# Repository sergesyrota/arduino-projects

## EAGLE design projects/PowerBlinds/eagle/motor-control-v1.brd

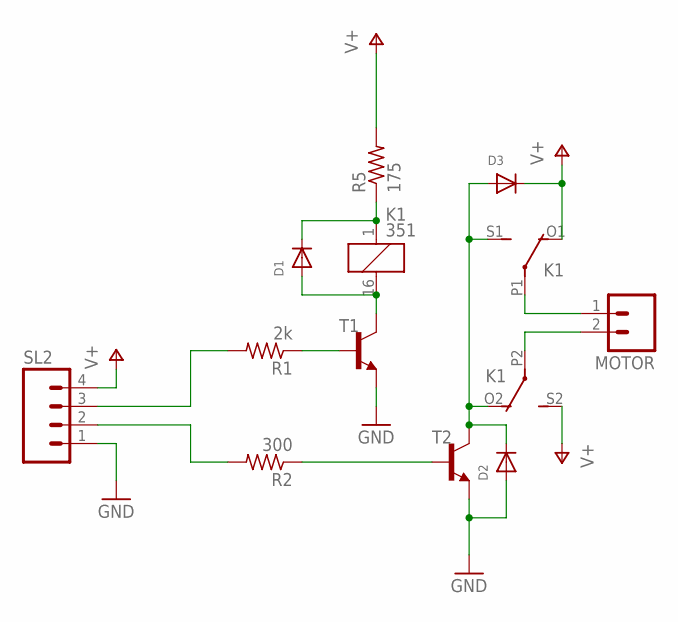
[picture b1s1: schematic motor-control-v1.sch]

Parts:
D1, D2, D3: DIODESMA; SMADIODE
K1: 351
MOTOR: M02; 02P
R1: 2k; R0603
R2: 300; R0603
R5: 175; R0603
SL2: M04; 04P
T1, T2: BC808-NPN-SOT23-BEC; SOT23-BEC

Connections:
GND: D2.A, SL2.1, T1.E, T2.E
unnamed: R2.2, SL2.2
unnamed: R1.2, SL2.3
unnamed: K1.P1, MOTOR.1
unnamed: K1.P2, MOTOR.2
unnamed: D2.C, D3.A, K1.O2 (O), K1.S1 (S), T2.C
unnamed: D1.A, K1.16 (2), T1.C
unnamed: D1.C, K1.1, R5.1
unnamed: R1.1, T1.B
unnamed: R2.1, T2.B
V+: D3.C, K1.O1 (O), K1.S2 (S), R5.2, SL2.4

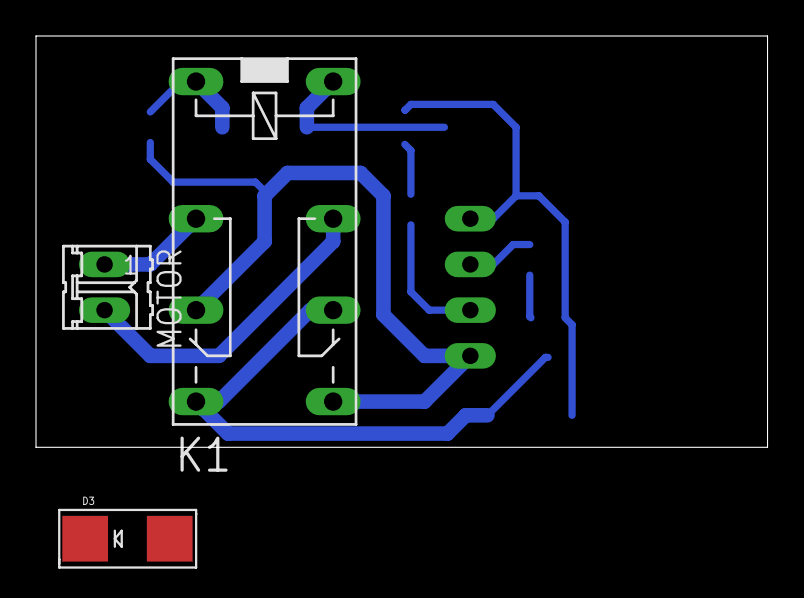
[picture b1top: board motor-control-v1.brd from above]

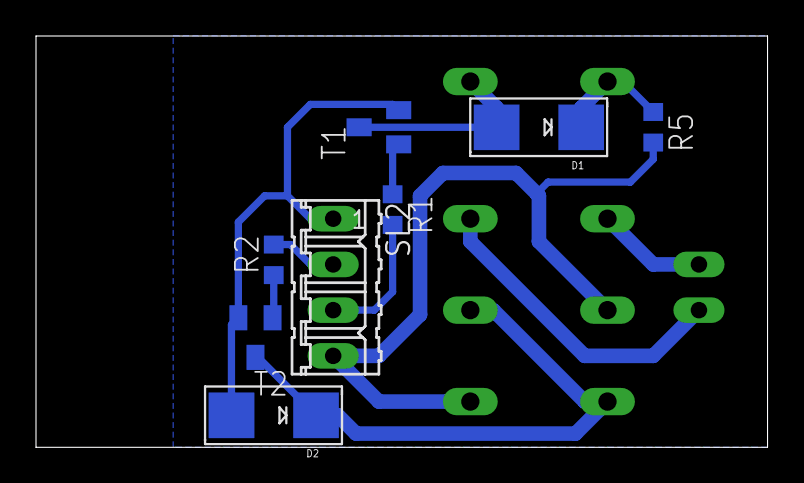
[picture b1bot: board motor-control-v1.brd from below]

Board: 2 copper layers, 40.6 x 22.9 mm, 11 parts (8 on the bottom side), 11 nets.

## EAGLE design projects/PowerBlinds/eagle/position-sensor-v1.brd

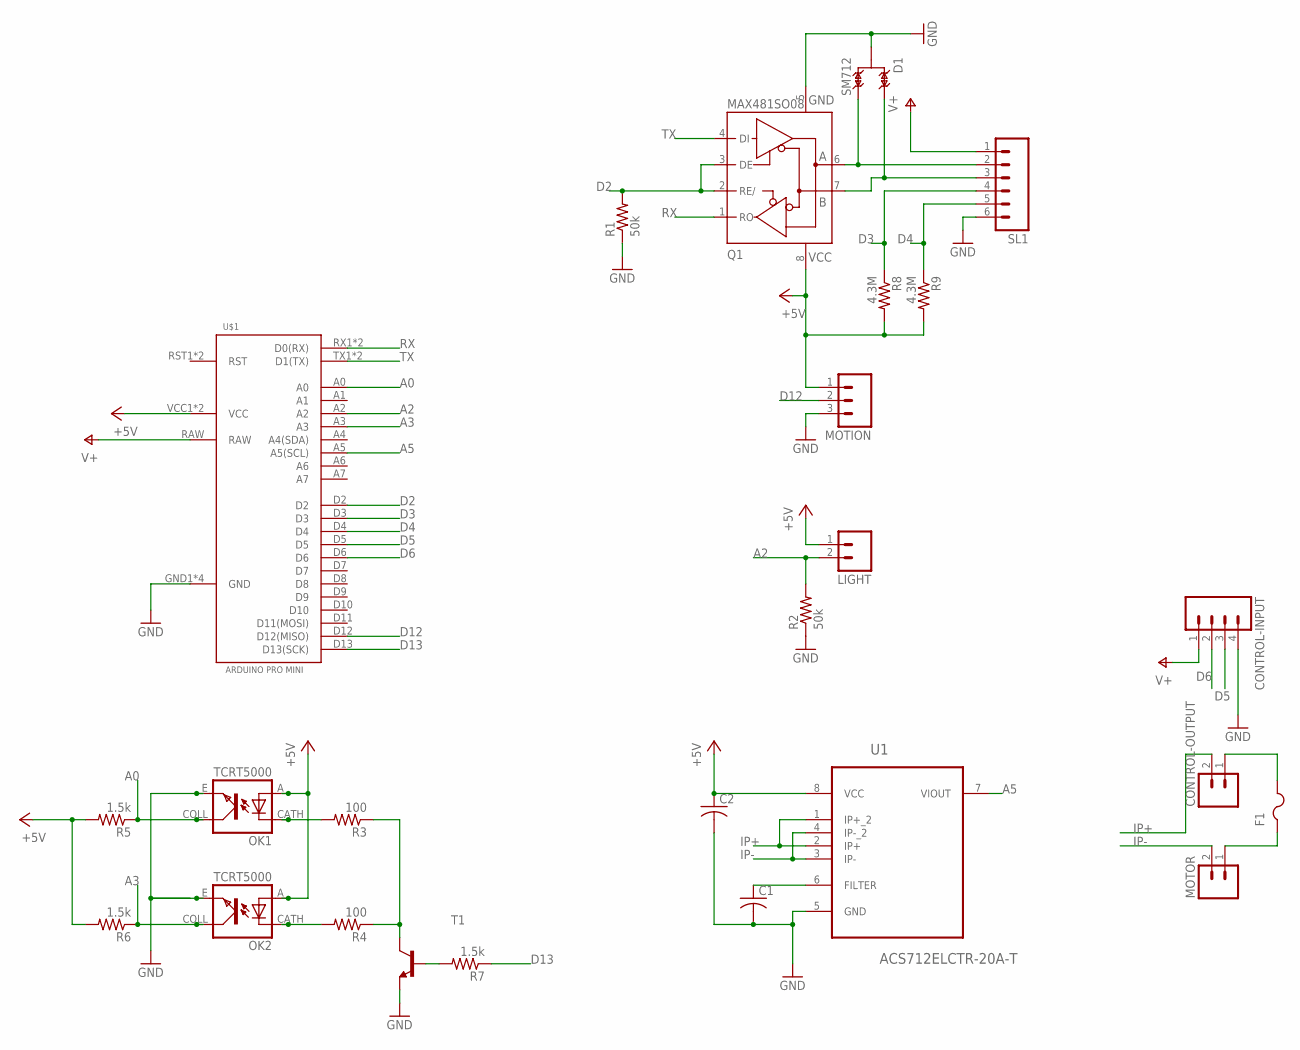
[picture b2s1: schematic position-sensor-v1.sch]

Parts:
C1, C2: C-USC0603K; C0603K
CONTROL-INPUT: M04; 04P
CONTROL-OUTPUT: M02; 02P
D1: SM712; SOT23-3
F1: PTCFUSE-1812; 1812
LIGHT: M02; 02P
MOTION: M03; 03P
MOTOR: M02; 02P
OK1, OK2: TCRT5000
Q1: MAX481SO08; SO08
R1, R2: 50k; R0603
R3, R4: 100; R0603
R5, R6, R7: 1.5k; R0603
R8, R9: 4.3M; R0603
SL1: M06; 06P
T1: BC808-NPN-SOT23-BEC; SOT23-BEC
U1: ACS712ELCTR-20A-T; SOIC127P600X175-8N
U$1: ARDUINO-PRO-MINI

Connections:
+5V: C2.1, LIGHT.1, MOTION.1, OK1.A, OK2.A, Q1.8 (+5V), R5.2, R6.2, R8.2, R9.2, U1.8 (VCC), U$1.VCC1 (VCC), U$1.VCC2 (VCC)
A0: OK1.COLL (COL), R5.1, U$1.A0
A2: LIGHT.2, R2.2, U$1.A2
A3: OK2.COLL (COL), R6.1, U$1.A3
A5: U1.7 (VIOUT), U$1.A5 (A5(SCL))
D2: Q1.2 (RE/), Q1.3 (DE), R1.2, U$1.D2
D3: R8.1, SL1.4, U$1.D3
D4: R9.1, SL1.5, U$1.D4
D5: CONTROL-INPUT.3, U$1.D5
D6: CONTROL-INPUT.2, U$1.D6
D12: MOTION.2, U$1.D12 (D12(MISO))
D13: R7.1, U$1.D13 (D13(SCK))
GND: C1.2, C2.2, CONTROL-INPUT.4, D1.3, MOTION.3, OK1.E (EMI), OK2.E (EMI), Q1.5 (GND), R1.1, R2.1, SL1.6, T1.E, U1.5 (GND), U$1.GND1 (GND), U$1.GND2 (GND), U$1.GND3 (GND), U$1.GND4 (GND)
IP+: CONTROL-OUTPUT.2, U1.1 (IP+_2), U1.2 (IP+)
IP-: MOTOR.2, U1.3 (IP-), U1.4 (IP-_2)
unnamed: D1.1, Q1.6 (A), SL1.2
unnamed: D1.2, Q1.7 (B), SL1.3
unnamed: F1.1, MOTOR.1
unnamed: OK1.CATH (C), R3.2
unnamed: OK2.CATH (C), R4.2
unnamed: CONTROL-OUTPUT.1, F1.2
unnamed: R7.2, T1.B
unnamed: R3.1, R4.1, T1.C
unnamed: C1.1, U1.6 (FILTER)
RX: Q1.1 (RO), U$1.RX1 (D0(RX)), U$1.RX2 (D0(RX))
TX: Q1.4 (DI), U$1.TX1 (D1(TX)), U$1.TX2 (D1(TX))
V+: CONTROL-INPUT.1, SL1.1, U$1.RAW

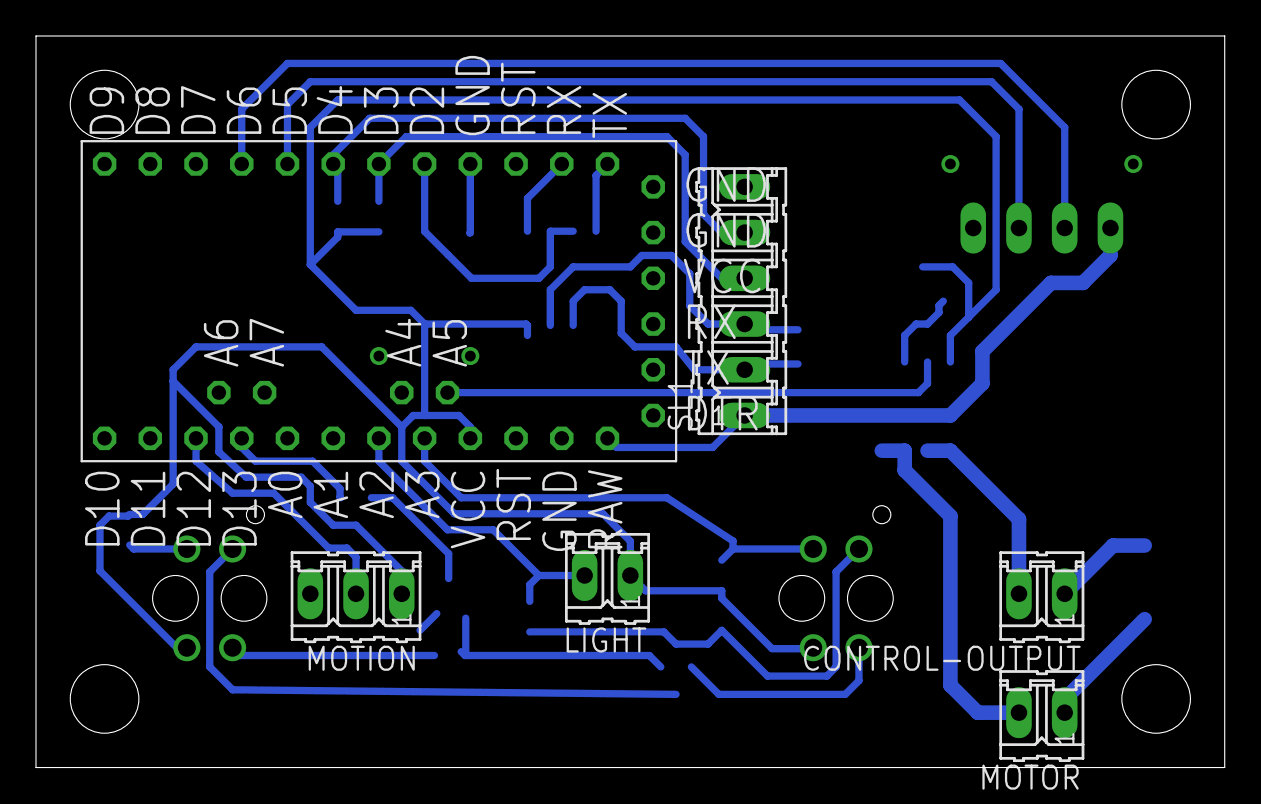
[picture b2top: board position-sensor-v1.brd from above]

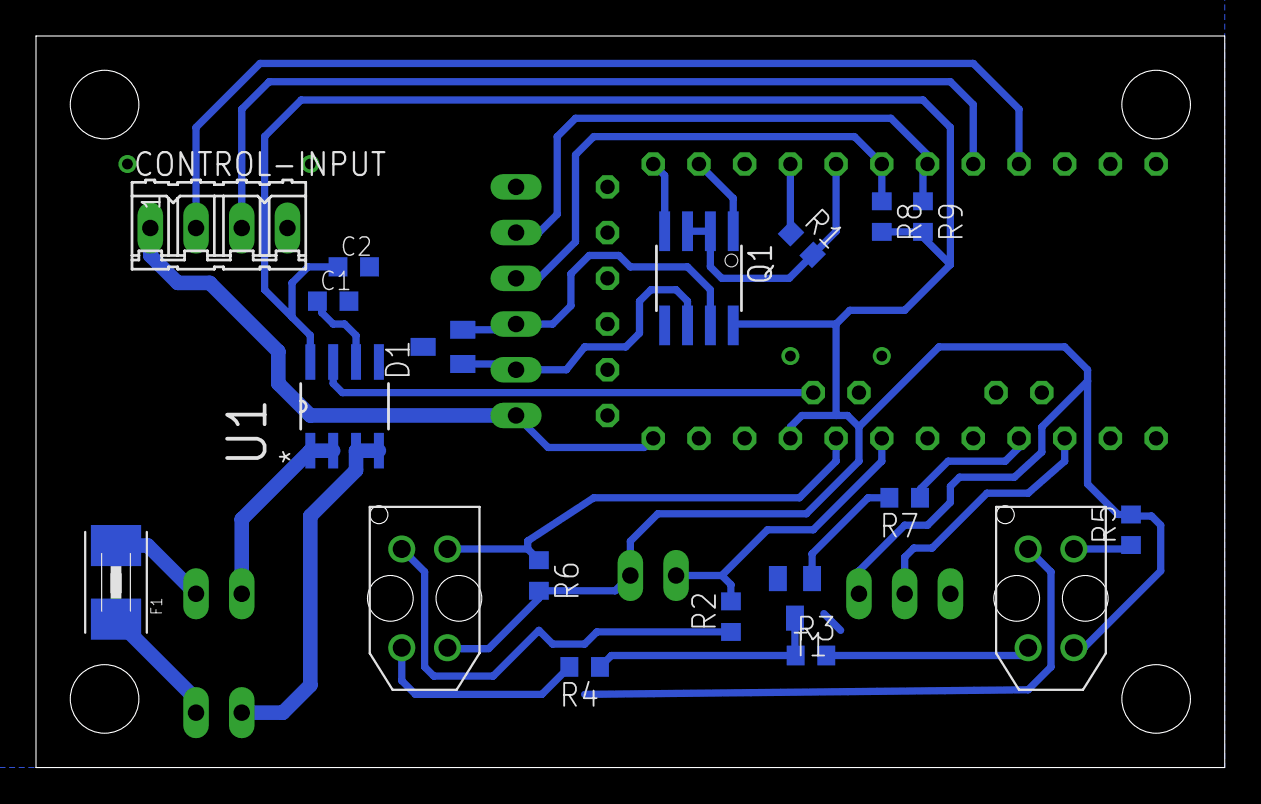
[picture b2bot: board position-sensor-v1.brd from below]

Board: 2 copper layers, 66.0 x 40.6 mm, 25 parts (19 on the bottom side), 27 nets.

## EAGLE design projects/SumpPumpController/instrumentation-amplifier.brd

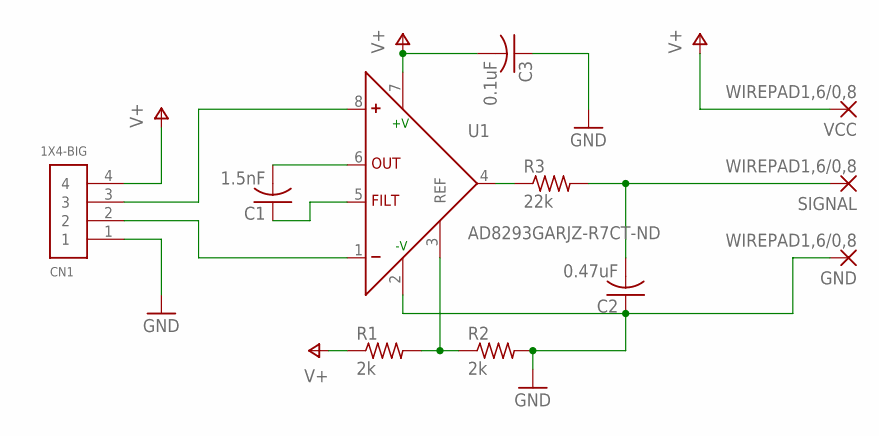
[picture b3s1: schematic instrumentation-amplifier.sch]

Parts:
C1: 1.5nF; C025-024X044
C2: 0.47uF; C050-024X044
C3: 0.1uF; C050-024X044
CN1: 1X4-BIG; 1X04-BIG
GND: WIREPAD1,6/0,8; 1,6/0,8
R1, R2: 2k; R0603
R3: 22k; R0603
SIGNAL: WIREPAD1,6/0,8; 1,6/0,8
U1: AD8293GARJZ-R7CT-ND; SOT23-8
VCC: WIREPAD1,6/0,8; 1,6/0,8

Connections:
GND: C2.1, C3.1, CN1.1, GND.1, R2.2, U1.2 (-V)
unnamed: C1.2, U1.6 (OUT)
unnamed: C1.1, U1.5 (FILT)
unnamed: R1.2, R2.1, U1.3 (REF)
unnamed: C2.2, R3.2, SIGNAL.1
unnamed: CN1.3, U1.8 (+)
unnamed: CN1.2, U1.1 (-)
unnamed: R3.1, U1.4 (ADC-OUT)
V+: C3.2, CN1.4, R1.1, U1.7 (+V), VCC.1

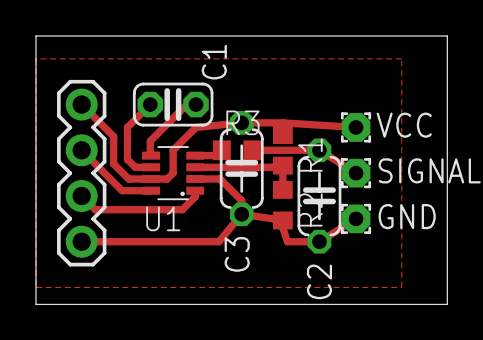
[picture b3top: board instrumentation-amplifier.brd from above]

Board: 2 copper layers, 22.9 x 14.9 mm, 11 parts (0 on the bottom side), 9 nets.

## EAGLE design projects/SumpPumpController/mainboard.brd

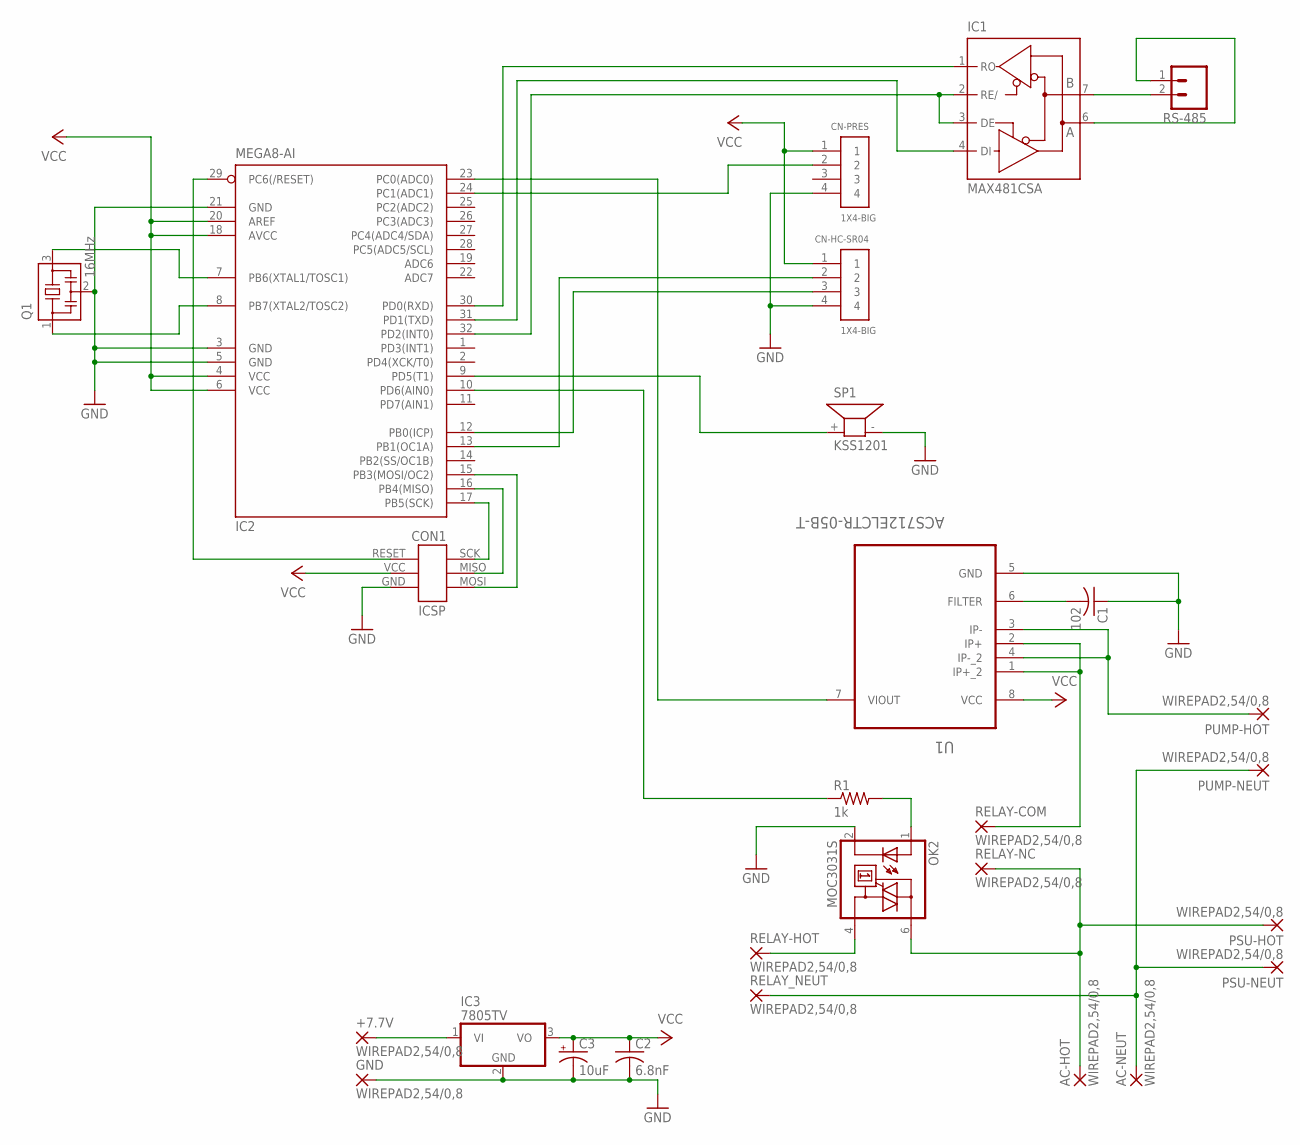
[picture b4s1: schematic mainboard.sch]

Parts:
+7.7V: WIREPAD2,54/0,8; 2,54/0,8
AC-HOT: WIREPAD2,54/0,8; 2,54/0,8
AC-NEUT: WIREPAD2,54/0,8; 2,54/0,8
C1: 102; C025-024X044
C2: 6.8nF; C050-024X044
C3: 10uF; E1,8-4
CN-HC-SR04: 1X4-BIG; 1X04-BIG
CN-PRES: 1X4-BIG; 1X04-BIG
CON1: ICSP-HEADER
GND: WIREPAD2,54/0,8; 2,54/0,8
IC1: MAX481CSA; SO08
IC2: MEGA8-AI; TQFP32-08
IC3: 7805TV; TO220V
OK2: MOC3031S; DIL6-SMD
PSU-HOT: WIREPAD2,54/0,8; 2,54/0,8
PSU-NEUT: WIREPAD2,54/0,8; 2,54/0,8
PUMP-HOT: WIREPAD2,54/0,8; 2,54/0,8
PUMP-NEUT: WIREPAD2,54/0,8; 2,54/0,8
Q1: 16MHz; RESONATOR
R1: 1k; R0603
RELAY-COM: WIREPAD2,54/0,8; 2,54/0,8
RELAY-HOT: WIREPAD2,54/0,8; 2,54/0,8
RELAY-NC: WIREPAD2,54/0,8; 2,54/0,8
RELAY_NEUT: WIREPAD2,54/0,8; 2,54/0,8
RS-485: M02; 02P
SP1: KSS1201
U1: ACS712ELCTR-05B-T; SOIC127P600X175-8N

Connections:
GND: C1.1, C2.2, C3.-, CN-HC-SR04.4, CN-PRES.4, CON1.GND, GND.1, IC1.5 (GND), IC2.3 (GND), IC2.5 (GND), IC2.21 (GND), IC3.2 (GND), OK2.2 (C), Q1.2, SP1.- (2), U1.5 (GND)
unnamed: IC2.7 (PB6(XTAL1/TOSC1)), Q1.3
unnamed: IC2.8 (PB7(XTAL2/TOSC2)), Q1.1
unnamed: CON1.SCK, IC2.17 (PB5(SCK))
unnamed: CON1.MISO, IC2.16 (PB4(MISO))
unnamed: CON1.MOSI, IC2.15 (PB3(MOSI/OC2))
unnamed: CON1.RESET, IC2.29 (PC6(/RESET))
unnamed: C1.2, U1.6 (FILTER)
unnamed: PUMP-HOT.1, U1.3 (IP-), U1.4 (IP-_2)
unnamed: +7.7V.1, IC3.1 (VI)
unnamed: AC-HOT.1, OK2.6 (A2), PSU-HOT.1, RELAY-NC.1
unnamed: AC-NEUT.1, PSU-NEUT.1, PUMP-NEUT.1, RELAY_NEUT.1
unnamed: OK2.4 (A1), RELAY-HOT.1
unnamed: IC2.9 (PD5(T1)), SP1.+ (1)
unnamed: IC2.23 (PC0(ADC0)), U1.7 (VIOUT)
unnamed: OK2.1 (A), R1.2
unnamed: IC2.10 (PD6(AIN0)), R1.1
unnamed: CN-PRES.2, IC2.24 (PC1(ADC1))
unnamed: CN-HC-SR04.2, IC2.13 (PB1(OC1A))
unnamed: CN-HC-SR04.3, IC2.12 (PB0(ICP))
unnamed: IC1.7 (B), RS-485.2
unnamed: IC1.6 (A), RS-485.1
unnamed: IC1.2 (RE/), IC1.3 (DE), IC2.32 (PD2(INT0))
unnamed: IC1.1 (RO), IC2.30 (PD0(RXD))
unnamed: IC1.4 (DI), IC2.31 (PD1(TXD))
RELAY-COM: RELAY-COM.1, U1.1 (IP+_2), U1.2 (IP+)
VCC: C2.1, C3.+, CN-HC-SR04.1, CN-PRES.1, CON1.VCC (+5V), IC1.8 (VCC), IC2.4 (VCC), IC2.6 (VCC), IC2.18 (AVCC), IC2.20 (AREF), IC3.3 (VO), U1.8 (VCC)

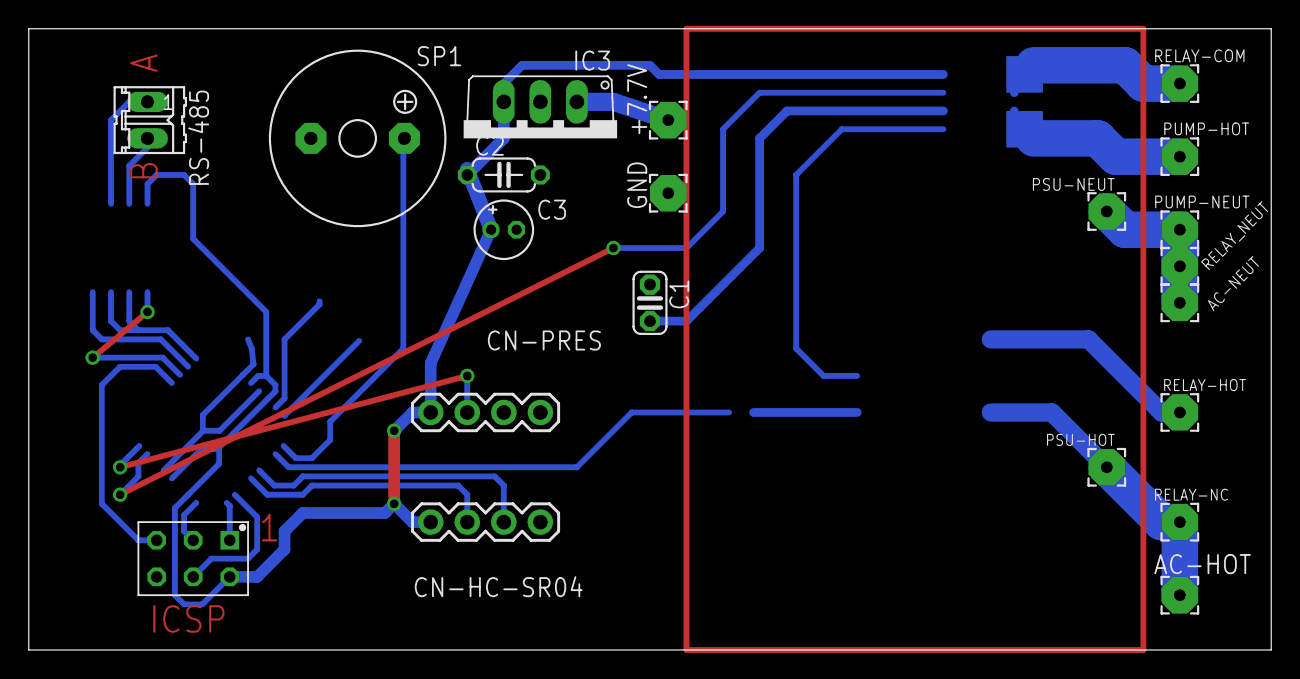
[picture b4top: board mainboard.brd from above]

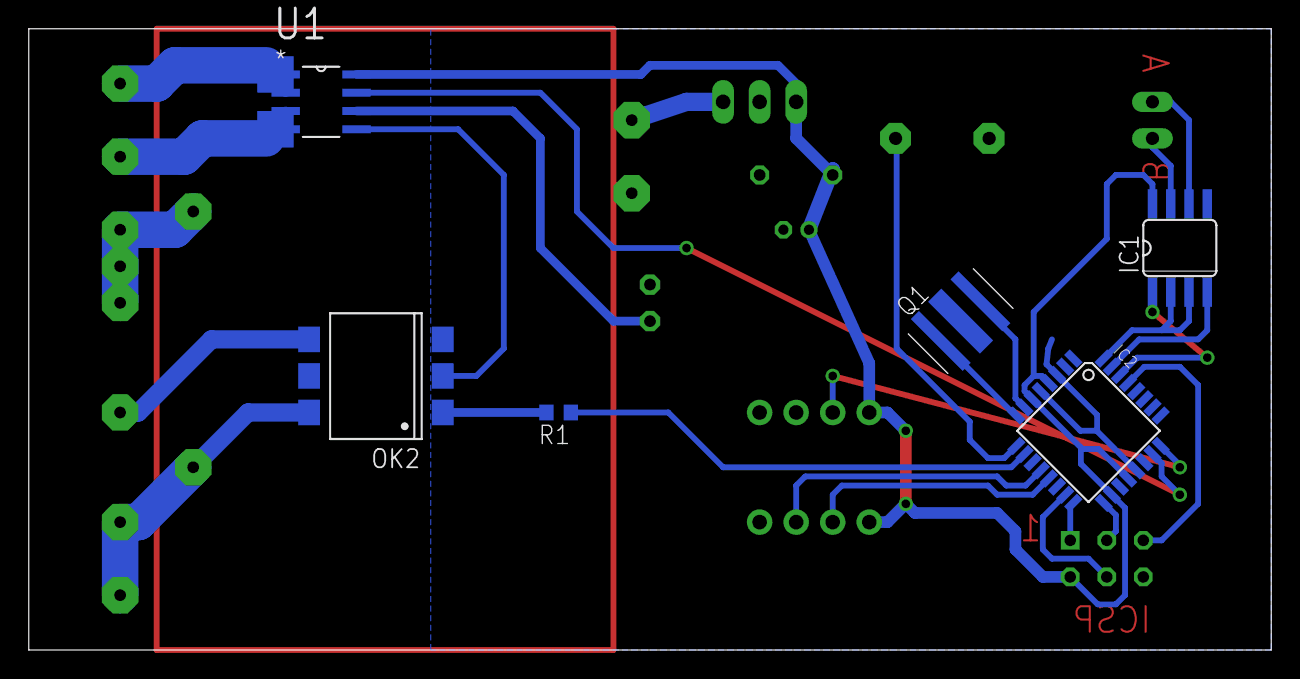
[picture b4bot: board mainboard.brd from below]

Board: 2 copper layers, 86.4 x 43.2 mm, 27 parts (6 on the bottom side), 27 nets.

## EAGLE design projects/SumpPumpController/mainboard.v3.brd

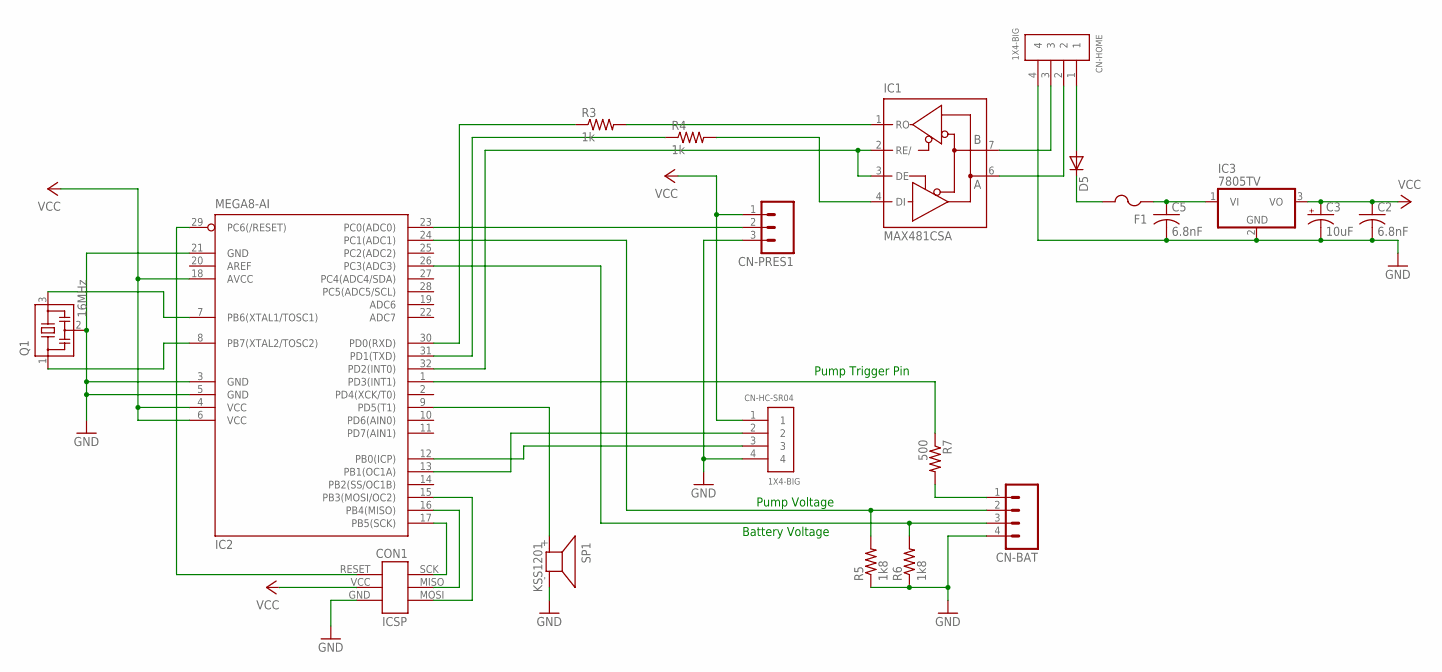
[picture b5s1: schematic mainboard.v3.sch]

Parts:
C2, C5: 6.8nF; C050-024X044
C3: 10uF; E1,8-4
CN-BAT: M04; 04P
CN-HC-SR04: 1X4-BIG; 1X04-BIG
CN-HOME: 1X4-BIG; 1X04-BIG
CN-PRES1: M03; 03P
CON1: ICSP-HEADER
D5: DIODE-MICROMELF-W; MICROMELF-W
F1: PTCFUSE-1206; R1206
IC1: MAX481CSA; SO08
IC2: MEGA8-AI; TQFP32-08
IC3: 7805TV; TO220V
Q1: 16MHz; RESONATOR
R3, R4: 1k; R0603
R5, R6: 1k8; R0603
R7: 500; R0603
SP1: KSS1201

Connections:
GND: C2.2, C3.-, C5.2, CN-BAT.4, CN-HC-SR04.4, CN-HOME.4, CN-PRES1.3, CON1.GND, IC1.5 (GND), IC2.3 (GND), IC2.5 (GND), IC2.21 (GND), IC3.2 (GND), Q1.2, R5.1, R6.1, SP1.- (2)
unnamed: IC2.7 (PB6(XTAL1/TOSC1)), Q1.3
unnamed: IC2.8 (PB7(XTAL2/TOSC2)), Q1.1
unnamed: CON1.SCK, IC2.17 (PB5(SCK))
unnamed: CON1.MISO, IC2.16 (PB4(MISO))
unnamed: CON1.MOSI, IC2.15 (PB3(MOSI/OC2))
unnamed: CON1.RESET, IC2.29 (PC6(/RESET))
unnamed: C5.1, F1.1, IC3.1 (VI)
unnamed: CN-HOME.1, D5.A
unnamed: D5.C, F1.2
unnamed: IC2.1 (PD3(INT1)), R7.1
unnamed: IC2.9 (PD5(T1)), SP1.+ (1)
unnamed: IC1.1 (RO), R3.2
unnamed: IC1.4 (DI), R4.2
unnamed: CN-BAT.1, R7.2
unnamed: CN-PRES1.2, IC2.23 (PC0(ADC0))
unnamed: CN-HC-SR04.2, IC2.13 (PB1(OC1A))
unnamed: CN-HC-SR04.3, IC2.12 (PB0(ICP))
unnamed: CN-HOME.3, IC1.7 (B)
unnamed: CN-BAT.3, IC2.26 (PC3(ADC3)), R6.2
unnamed: IC1.2 (RE/), IC1.3 (DE), IC2.32 (PD2(INT0))
unnamed: IC2.30 (PD0(RXD)), R3.1
unnamed: IC2.31 (PD1(TXD)), R4.1
unnamed: CN-BAT.2, IC2.24 (PC1(ADC1)), R5.2
unnamed: CN-HOME.2, IC1.6 (A)
VCC: C2.1, C3.+, CN-HC-SR04.1, CN-PRES1.1, CON1.VCC (+5V), IC1.8 (VCC), IC2.4 (VCC), IC2.6 (VCC), IC2.18 (AVCC), IC3.3 (VO)

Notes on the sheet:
Battery Voltage
Pump Voltage
Pump Trigger Pin

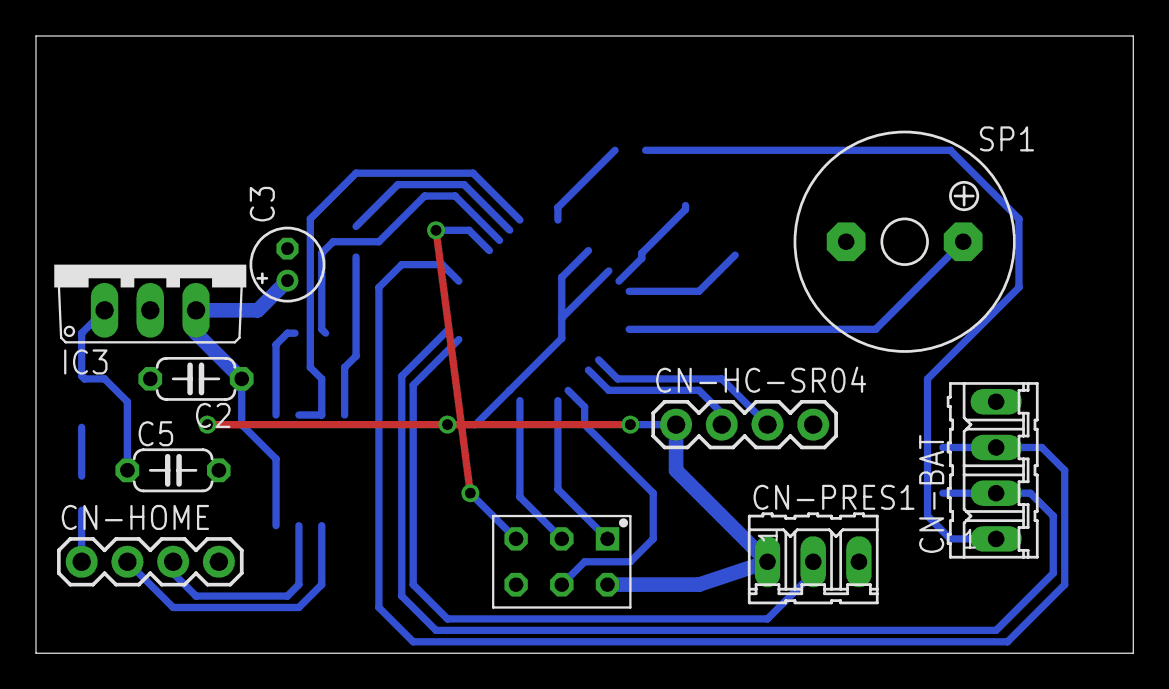
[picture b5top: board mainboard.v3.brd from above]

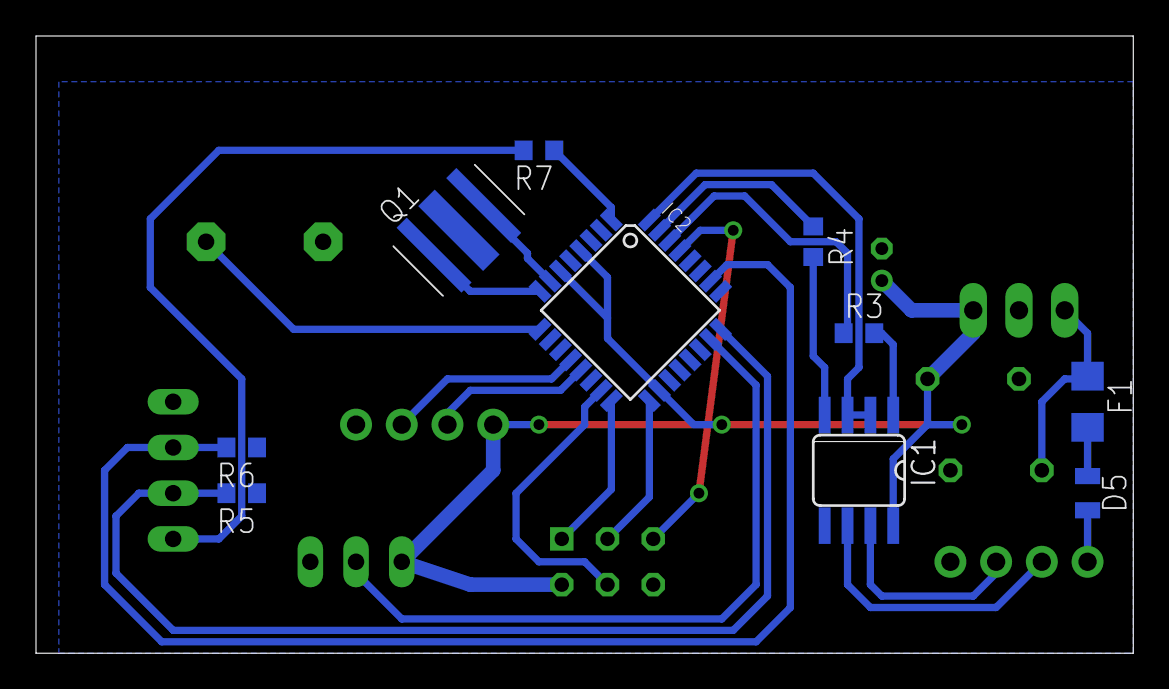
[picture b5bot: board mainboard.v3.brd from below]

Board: 2 copper layers, 61.0 x 34.3 mm, 20 parts (10 on the bottom side), 26 nets.
